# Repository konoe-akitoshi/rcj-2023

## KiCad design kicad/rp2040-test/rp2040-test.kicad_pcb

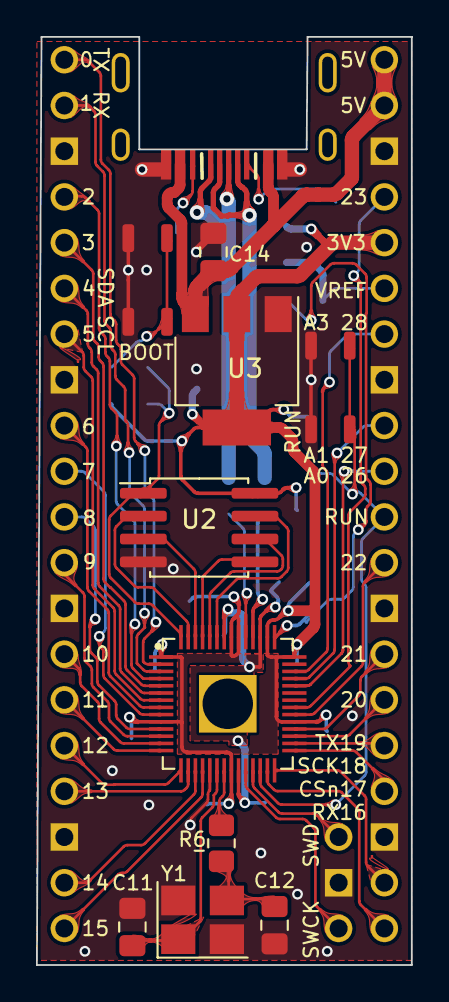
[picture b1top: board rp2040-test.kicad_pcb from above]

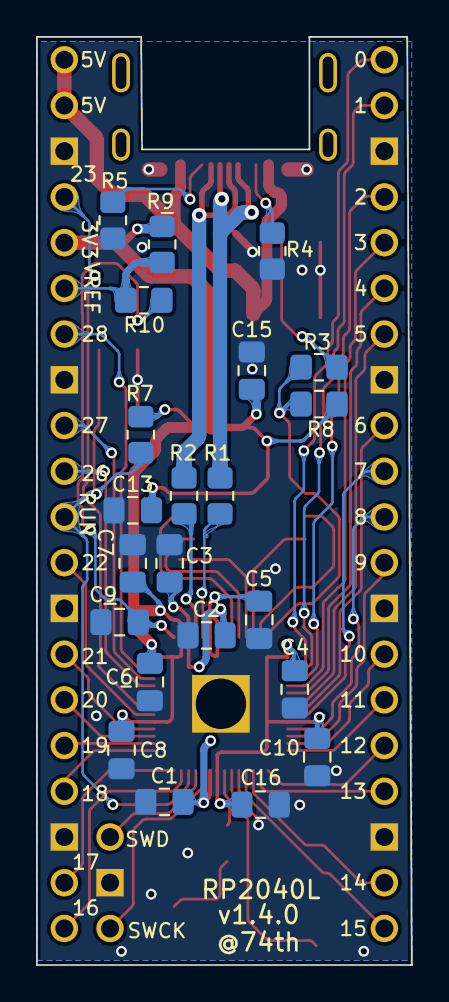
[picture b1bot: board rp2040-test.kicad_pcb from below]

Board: 2 copper layers, 20.8 x 51.6 mm, 36 parts (22 on the bottom side), 52 nets.

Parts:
C1, C2, C4, C6, C7, C8, C10, C13, C16: 100nF; Capacitor_0805_2012
C3, C5, C9: 1uF; Capacitor_0805_2012
C11, C12: 27pF; Capacitor_0805_2012
C14, C15: 10uF; Capacitor_0805_2012
J1: USB2.0_C_v3; USB-C-12-Pin-MidMount-ali-v4
J2: SWD; SWD_PIN
P2, P3: 20Pin; SC0915-LIKE
R1, R2: 27.4R; Register_0805_2012
R3, R6, R7: 1kR; Register_0805_2012
R4, R5: 5.1kR; Register_0805_2012
R8: 10kR; Register_0805_2012
R9: 200R; Register_0805_2012
R10: 1R; Register_0805_2012
SW1, SW2: SW_Push; SKRPABE010
U1: RP2040; RP2040_hand
U2: W25Q128JVS; W25Q16-128JV-SOIC
U3: AZ1117-3.3; SOT-223-3_TabPin2
Y1: Crystal_GND24; Crystal_SMD_3225-4Pin_3.2x2.5mm_HandSoldering

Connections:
0: P2.1, U1.2 (GPIO0)
1: P2.2, U1.3 (GPIO1)
2: P2.4, U1.4 (GPIO2)
3: P2.5, U1.5 (GPIO3)
4: P2.6, U1.6 (GPIO4)
5: P2.7, U1.7 (GPIO5)
6: P2.9, U1.8 (GPIO6)
7: P2.10, U1.9 (GPIO7)
8: P2.11, U1.11 (GPIO8)
9: P2.12, U1.12 (GPIO9)
10: P2.14, U1.13 (GPIO10)
11: P2.15, U1.14 (GPIO11)
12: P2.16, U1.15 (GPIO12)
13: P2.17, U1.16 (GPIO13)
14: P2.19, U1.17 (GPIO14)
15: P2.20, U1.18 (GPIO15)
16: P3.20, U1.27 (GPIO16)
17: P3.19, U1.28 (GPIO17)
18: P3.17, U1.29 (GPIO18)
19: P3.16, U1.30 (GPIO19)
20: P3.15, U1.31 (GPIO20)
21: P3.14, U1.32 (GPIO21)
22: P3.12, U1.34 (GPIO22)
23: P3.4, U1.35 (GPIO23)
26: P3.10, U1.38 (GPIO26_ADC0)
27: P3.9, U1.39 (GPIO27_ADC1)
28: P3.7, U1.40 (GPIO28_ADC2)
+1V1: C1.1, C2.1, C3.1, U1.23 (DVDD), U1.45 (VREG_VOUT), U1.50 (DVDD)
+3V3: C4.1, C5.1, C6.1, C7.1, C8.1, C10.1, C13.1, C15.1, C16.1, P3.5, R7.2, R8.2, R9.2, U1.1 (IOVDD), U1.10 (IOVDD), U1.22 (IOVDD), U1.33 (IOVDD), U1.42 (IOVDD), U1.44 (VREG_IN), U1.48 (USB_VDD), U1.49 (IOVDD), U2.8 (VCC), U3.2 (VO)
+5V: C14.1, J1.1 (VBUS), P3.1, P3.2, U3.3 (VI)
ADC_VREF: P3.6, R9.1, R10.2
GND: C1.2, C2.2, C3.2, C4.2, C5.2, C6.2, C7.2, C8.2, C9.2, C10.2, C11.1, C12.1, C13.2, C14.2, C15.2, C16.2, J1.4 (GND), J2.2 (GND), P2.3, P2.8, P2.13, P2.18, P3.3, P3.8, P3.13, P3.18, R4.2, R5.2, SW1.1, SW2.1, U1.19 (TESTEN), U1.57 (GND), U2.4 (GND), U3.1 (GND), Y1.2, Y1.4
unnamed: C9.1, R10.1, U1.43 (ADC_AVDD)
unnamed: C12.2, R6.2, Y1.3
unnamed: J1.5 (CC1), R5.1
unnamed: J1.6 (CC2), R4.1
unnamed: J2.1 (SWCLK), U1.24 (SWCLK)
unnamed: J2.3 (SWDIO), U1.25 (SWD)
unnamed: R1.1, U1.47 (USB_DP)
unnamed: R2.1, U1.46 (USB_DM)
unnamed: R3.1, SW1.2
QSPI_CLK: U1.52 (QSPI_SCLK), U2.6 (CLK)
QSPI_SD0: U1.53 (QSPI_SD0), U2.5 (DI(IO0))
QSPI_SD1: U1.55 (QSPI_SD1), U2.2 (DO(IO1))
QSPI_SD2: U1.54 (QSPI_SD2), U2.3 (IO2)
QSPI_SD3: U1.51 (QSPI_SD3), U2.7 (IO3)
QSPI_SS: R3.2, R8.1, U1.56 (QSPI_SS), U2.1 (~CS)
USB_DM: J1.2 (D-), R2.2
USB_DP: J1.3 (D+), R1.2
XIN: C11.2, U1.20 (XIN), Y1.1
XOUT: R6.1, U1.21 (XOUT)
~RESET: P3.11, R7.1, SW2.2, U1.26 (RUN)

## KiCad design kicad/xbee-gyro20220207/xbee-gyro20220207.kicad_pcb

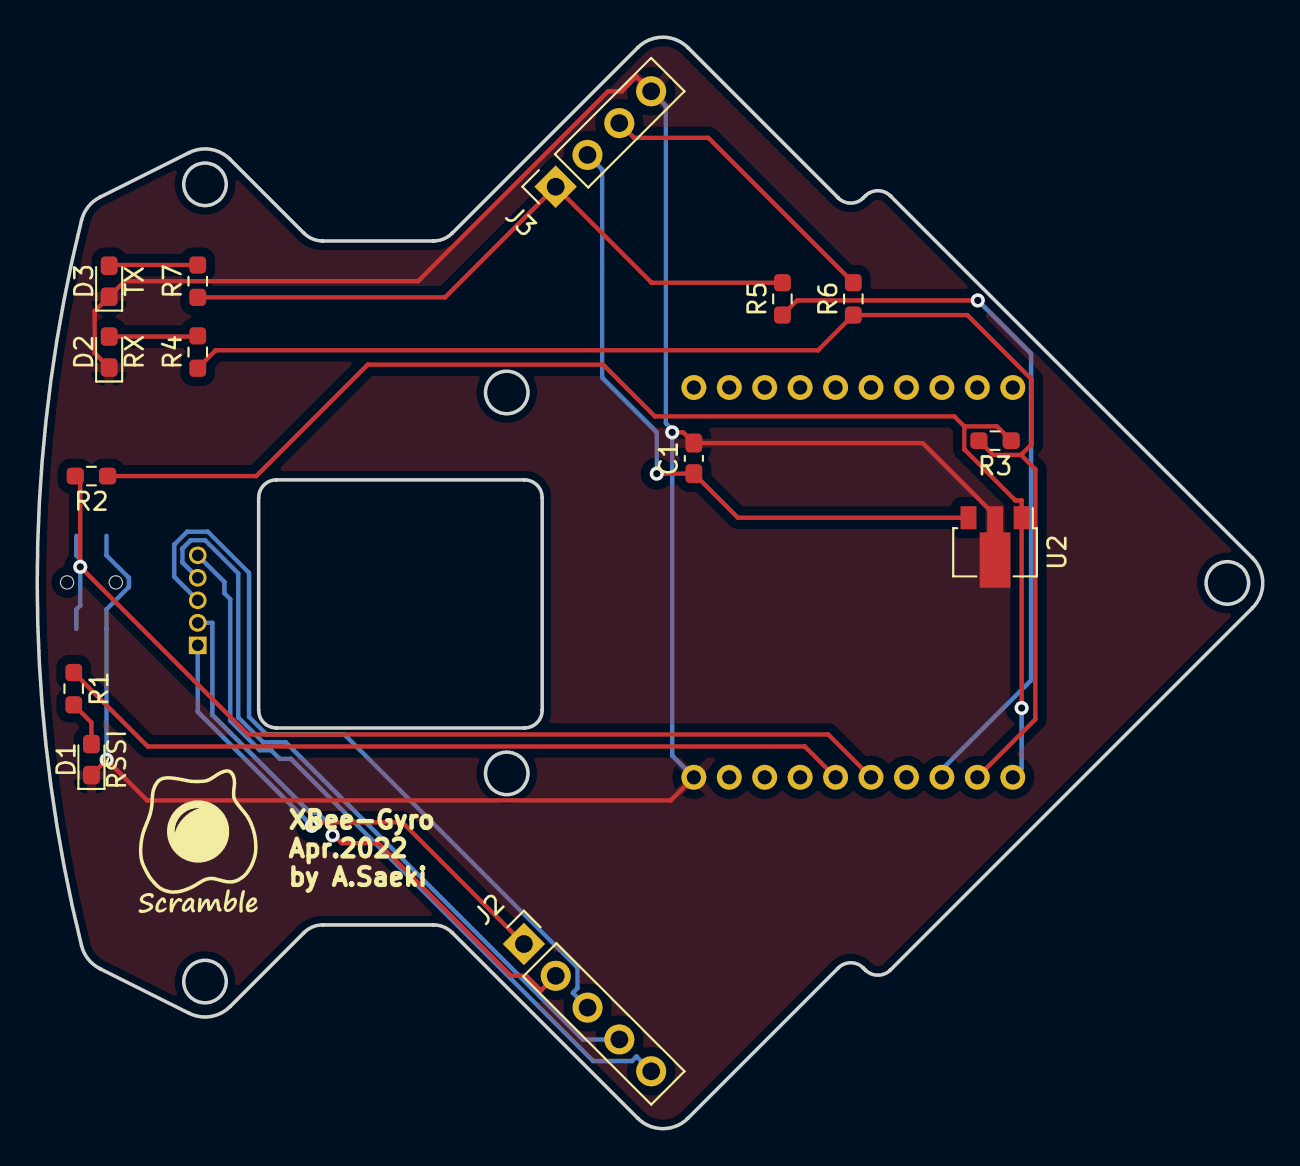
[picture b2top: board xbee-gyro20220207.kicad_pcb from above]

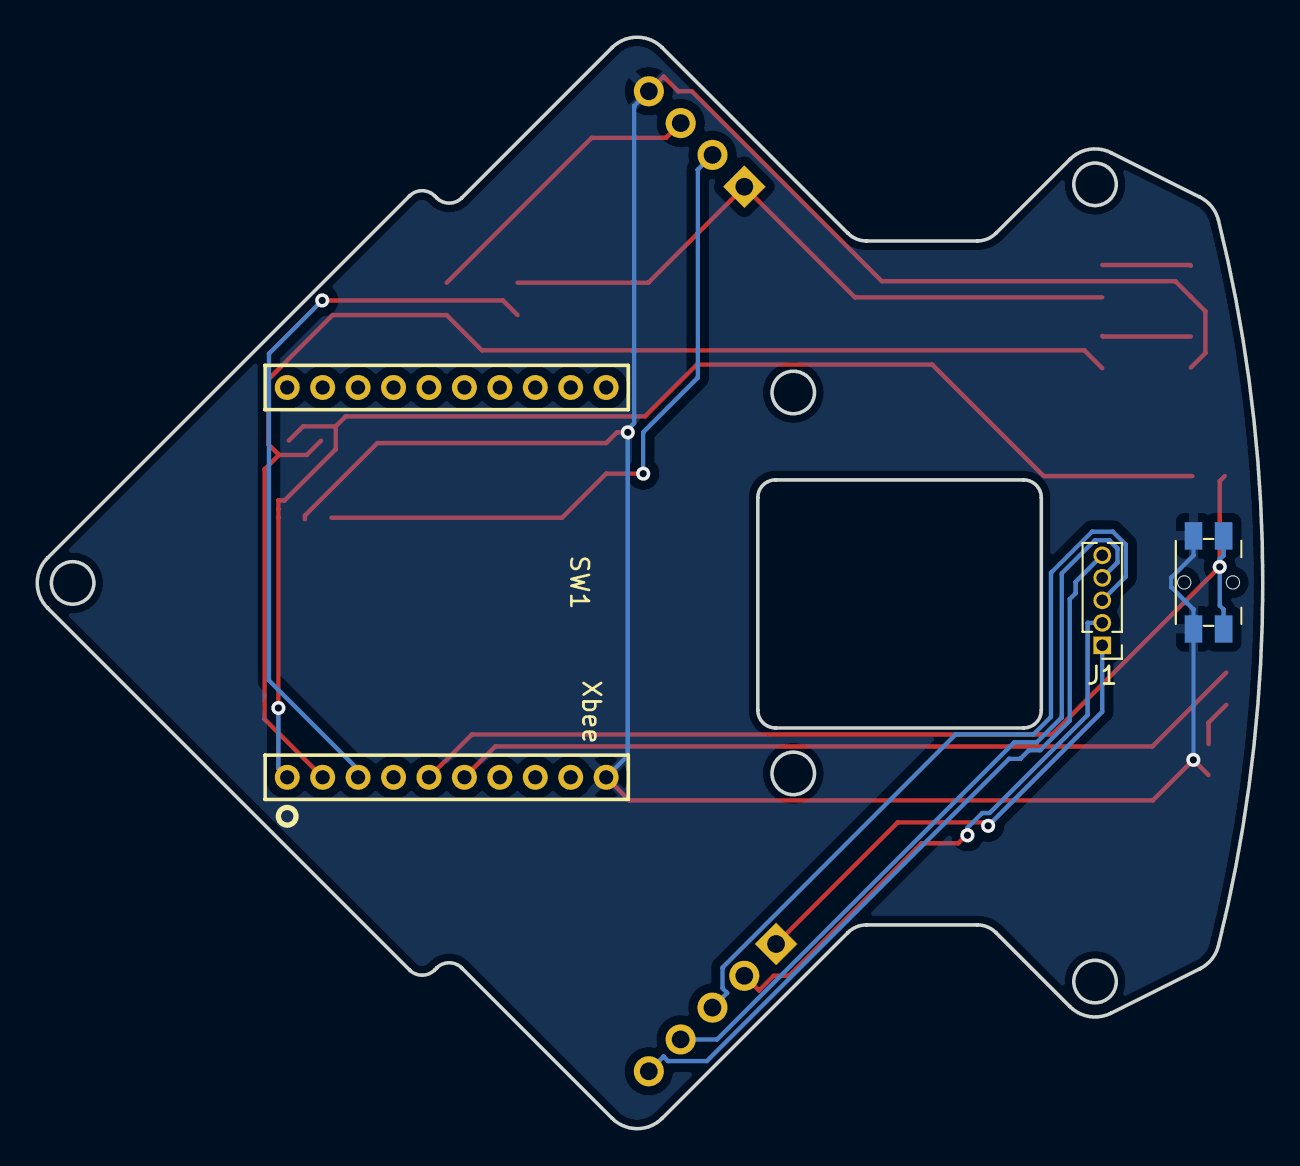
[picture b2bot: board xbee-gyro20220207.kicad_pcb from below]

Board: 2 copper layers, 69.2 x 61.6 mm, 17 parts (3 on the bottom side), 17 nets.

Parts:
C1: 0.1u; C_0603_1608Metric_Pad1.08x0.95mm_HandSolder
D1: RSSI; LED_0603_1608Metric_Pad1.05x0.95mm_HandSolder
D2: RX; LED_0603_1608Metric_Pad1.05x0.95mm_HandSolder
D3: TX; LED_0603_1608Metric_Pad1.05x0.95mm_HandSolder
J1: IMU_in; PinHeader_1x05_P1.27mm_Vertical
J2: IMU; PinSocket_1x05_P2.54mm_Vertical
J3: XBee; PinSocket_1x04_P2.54mm_Vertical
R1, R4, R7: 470; R_0603_1608Metric_Pad0.98x0.95mm_HandSolder
R2, R3, R5, R6: 10k; R_0603_1608Metric_Pad0.98x0.95mm_HandSolder
SW1: Reset; THAU13-AB-R
U1: XBEE-S2C
U2: XC6216D_SOT89; SOT-89-3

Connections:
+5V: C1.1, J3.2, U2.3 (IN)
GND: C1.2, D1.1 (K), D2.1 (K), D3.1 (K), J3.4, SW1.2, U1.10 (GND), U2.2 (GND)
unnamed: D1.2 (A), R1.2
unnamed: D2.2 (A), R4.2
unnamed: D3.2 (A), R7.2
unnamed: J1.1, J2.1
unnamed: J1.2, J2.2
unnamed: J1.3, J2.3
unnamed: J1.4, J2.4
unnamed: J1.5, J2.5
unnamed: J3.1, R5.2, R7.1
unnamed: J3.3, R6.2
unnamed: R1.1, U1.6 (RSSI)
unnamed: R2.1, R3.1, U1.1 (VDD), U2.1 (OUT)
unnamed: R2.2, SW1.1, U1.5 (RESET)
unnamed: R3.2, R4.1, R6.1, U1.2 (DOUT)
unnamed: R5.1, U1.3 (DIN)
